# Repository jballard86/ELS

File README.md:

# Electronic Lead Screw
    By Jeff Ballard

Anticipated features:
  - Metric / Inch threading
  - Metric / Inch feeding
  - Auto threading with 2 steppers
  - Auto turn to a specified diameter
  - Pendent Control with:
    - Manual Z control
    - Manual X control
  - Radius cutting
  - Ball cutting
  - chamfer cutting
  - Digital Dial replacements (pipe dream)

This Lead Screw is 100% untested at this point, the code works on a test stand that has the following:
  - 24v power supply
  - 12v power supply
  - Custom PCB w/ a Teensy 4.0
  - 1 stepper motor w/Driver
  - 1 DC motor w/encoder
  - various display/interface hardware

PCB is 100% operational on test board.  Cad files to come for mounting all components in a housing for mounting near the lathe.

Lathe installation will happen shortly.

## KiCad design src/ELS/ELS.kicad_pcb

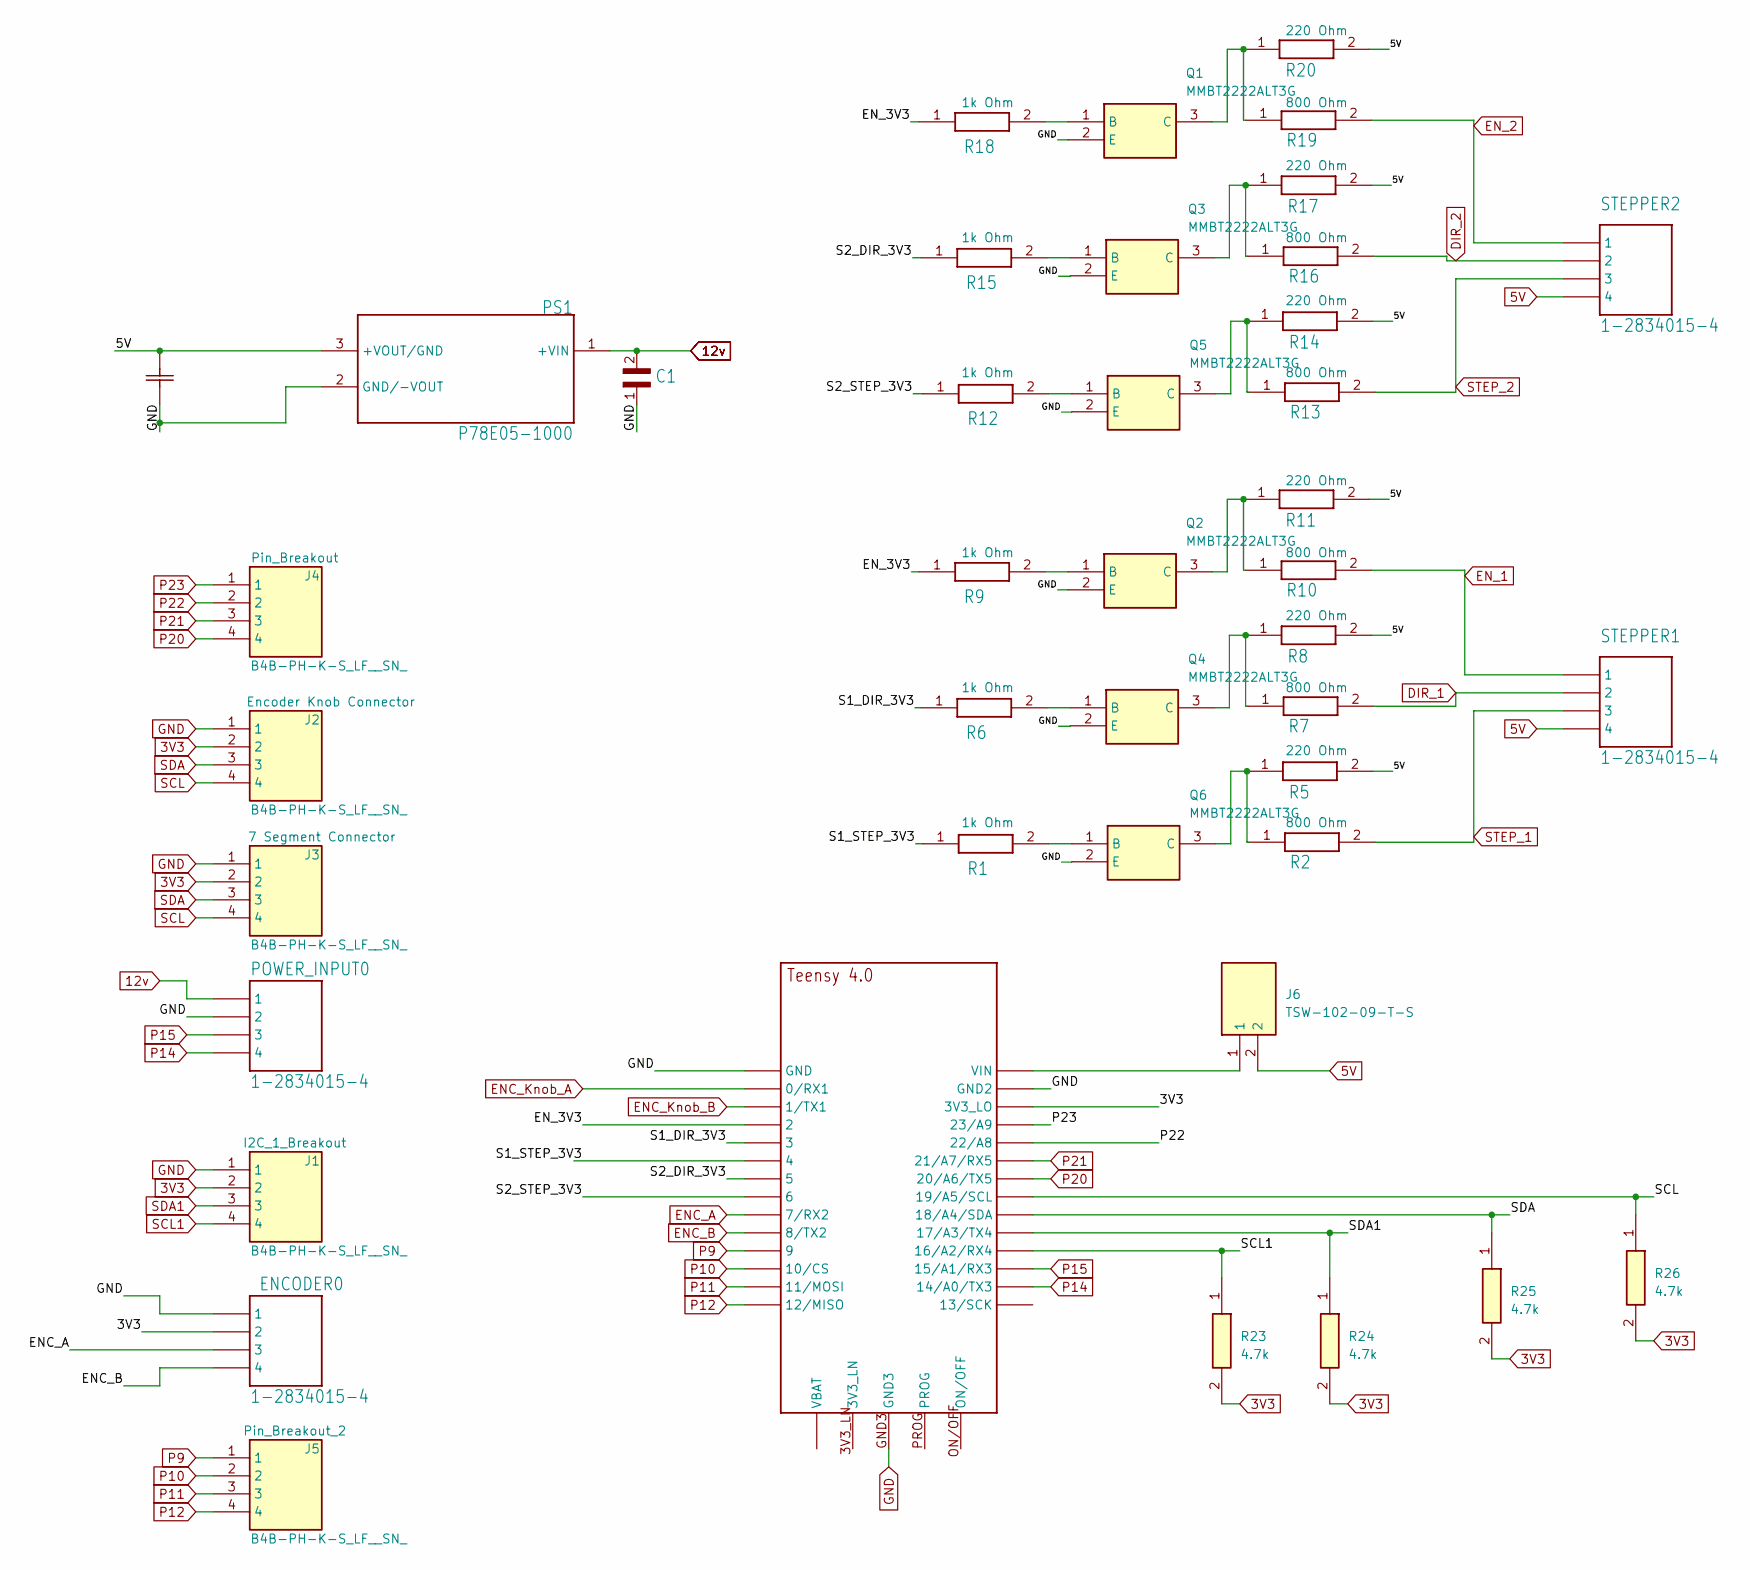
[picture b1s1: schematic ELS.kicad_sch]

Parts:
C1: CL31B106KBHNNNE; CAPC3216X140N
C2: CL32B226MOJNNNECAP_CL32_SAM-M; CAP_CL32_SAM-M
ENCODER0: 1-2834015-4; TE_1-2834015-4
J1, J2, J3, J4, J5: B4B-PH-K-S_LF__SN_; SHDR4W50P0X200_1X4_990X450X600P; Manufacturer_Part_Number B4B-PH-K-S(LF)(SN)
J6: TSW-102-09-T-S; TSW-102-XX-YY-S; Manufacturer_Part_Number TSW-102-09-T-S
POWER_INPUT0: 1-2834015-4; TE_1-2834015-4
PS1: P78E05-1000; CONV_P78E05-1000; VOLTAGE 5v
Q1, Q2, Q3, Q4, Q5, Q6: MMBT2222ALT3G; SOT96P237X111-3N; Mouser Part Number 863-MMBT2222ALT3G
R1, R6, R9, R12, R15, R18: CRCW12061K00FKEAC; RESC3216X60N
R2, R7, R10, R13, R16, R19: CR1206-FX-8250ELF; RESC3216X75N
R5, R8, R11, R14, R17, R20: CRCW1206220RFKEAC; RESC3216X60N
R23, R24, R25, R26: CRCW12064K70FKEBC; RESC3216X60N; Mouser Part Number 71-CRCW12064K70FKEBC
STEPPER1, STEPPER2: 1-2834015-4; TE_1-2834015-4
TEENSY_4.0: TEENSY_4.0

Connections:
3V3: ENCODER0.2_1 (2), ENCODER0.2_2 (2), J1.2, J2.2, J3.2, R23.2, R24.2, R25.2, R26.2, TEENSY_4.0.3V3_LO
5V: C2.2, J6.2, PS1.3 (+VOUT/GND), R5.2, R8.2, R11.2, R14.2, R17.2, R20.2, STEPPER1.4_1 (4), STEPPER1.4_2 (4), STEPPER2.4_1 (4), STEPPER2.4_2 (4)
12v: C1.2, POWER_INPUT0.1_1 (1), POWER_INPUT0.1_2 (1), PS1.1 (+VIN)
/EN_3V3: R9.1, R18.1, TEENSY_4.0.2
/S1_DIR_3V3: R6.1, TEENSY_4.0.3/CANTX (3)
/S1_STEP_3V3: R1.1, TEENSY_4.0.4/CANRX (4)
/S2_DIR_3V3: R15.1, TEENSY_4.0.5
/S2_STEP_3V3: R12.1, TEENSY_4.0.6
DIR_1: R7.2, STEPPER1.2_1 (2), STEPPER1.2_2 (2)
DIR_2: R16.2, STEPPER2.2_1 (2), STEPPER2.2_2 (2)
ENC_A: ENCODER0.3_1 (3), ENCODER0.3_2 (3), TEENSY_4.0.7 (7/RX2)
ENC_B: ENCODER0.4_1 (4), ENCODER0.4_2 (4), TEENSY_4.0.8 (8/TX2)
ENC_Knob_A: TEENSY_4.0.0/RX (0/RX1)
ENC_Knob_B: TEENSY_4.0.1/TX (1/TX1)
EN_1: R10.2, STEPPER1.1_1 (1), STEPPER1.1_2 (1)
EN_2: R19.2, STEPPER2.1_1 (1), STEPPER2.1_2 (1)
GND: C1.1, C2.1, ENCODER0.1_1 (1), ENCODER0.1_2 (1), J1.1, J2.1, J3.1, POWER_INPUT0.2_1 (2), POWER_INPUT0.2_2 (2), PS1.2 (GND/-VOUT), Q1.2 (E), Q2.2 (E), Q3.2 (E), Q4.2 (E), Q5.2 (E), Q6.2 (E), TEENSY_4.0.GND, TEENSY_4.0.GND2, TEENSY_4.0.GND3
unnamed: J6.1, TEENSY_4.0.VIN
unnamed: Q1.1 (B), R18.2
unnamed: Q1.3 (C), R19.1, R20.1
unnamed: Q2.1 (B), R9.2
unnamed: Q2.3 (C), R10.1, R11.1
unnamed: Q3.1 (B), R15.2
unnamed: Q3.3 (C), R16.1, R17.1
unnamed: Q4.1 (B), R6.2
unnamed: Q4.3 (C), R7.1, R8.1
unnamed: Q5.1 (B), R12.2
unnamed: Q5.3 (C), R13.1, R14.1
unnamed: Q6.1 (B), R1.2
unnamed: Q6.3 (C), R2.1, R5.1
P9: J5.1, TEENSY_4.0.9/CS (9)
P10: J5.2, TEENSY_4.0.10/CS
P11: J5.3, TEENSY_4.0.11/MOSI
P12: J5.4, TEENSY_4.0.12/MISO
P14: POWER_INPUT0.4_1 (4), POWER_INPUT0.4_2 (4), TEENSY_4.0.14/A0 (14/A0/TX3)
P15: POWER_INPUT0.3_1 (3), POWER_INPUT0.3_2 (3), TEENSY_4.0.15/A1 (15/A1/RX3)
P20: J4.4, TEENSY_4.0.20/A6 (20/A6/TX5)
P21: J4.3, TEENSY_4.0.21/A7 (21/A7/RX5)
P22: J4.2, TEENSY_4.0.22/A8
P23: J4.1, TEENSY_4.0.23/A9
SCL: J2.4, J3.4, R26.1, TEENSY_4.0.19/A5/SCL
SCL1: J1.4, R23.1, TEENSY_4.0.16/A2 (16/A2/RX4)
SDA: J2.3, J3.3, R25.1, TEENSY_4.0.18/A4/SDA
SDA1: J1.3, R24.1, TEENSY_4.0.17/A3 (17/A3/TX4)
STEP_1: R2.2, STEPPER1.3_1 (3), STEPPER1.3_2 (3)
STEP_2: R13.2, STEPPER2.3_1 (3), STEPPER2.3_2 (3)

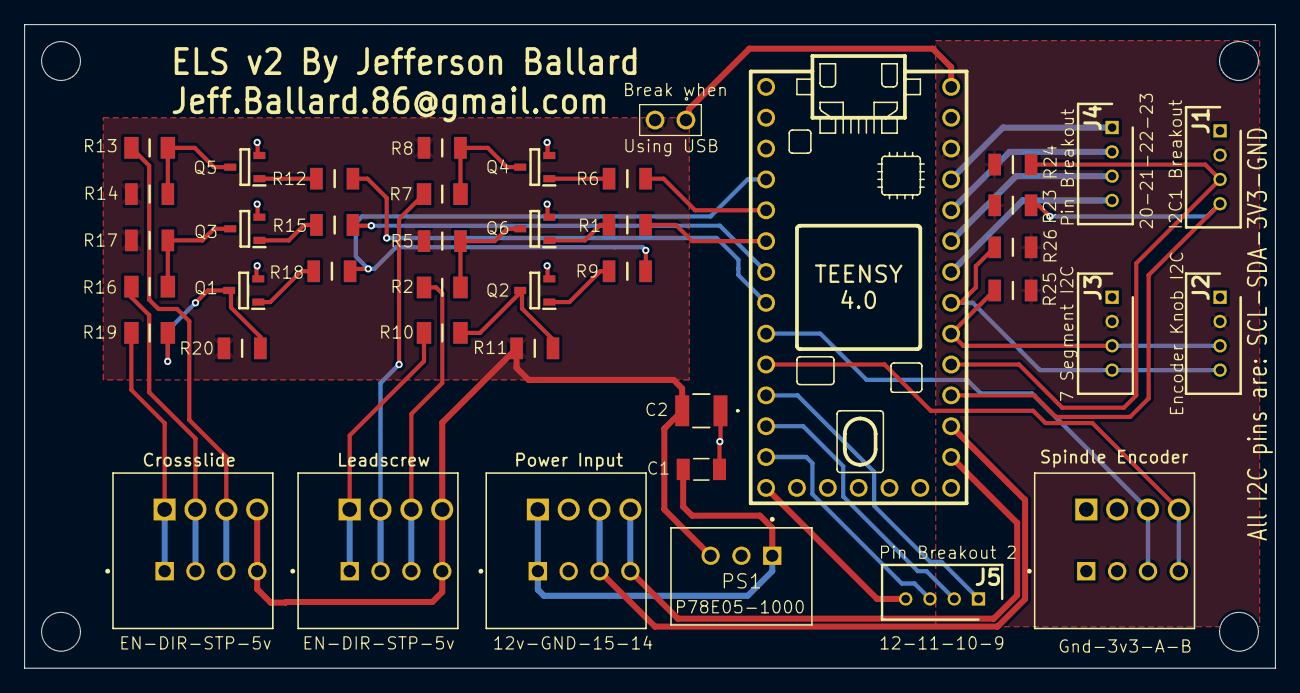
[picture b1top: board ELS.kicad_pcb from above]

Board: 2 copper layers, 103.0 x 53.0 mm, 42 parts (0 on the bottom side), 44 nets.

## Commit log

2023-05-29 initial
2023-05-29 test
2023-05-29 added auto thread menu, and thread depth calcs
2023-05-29 fixed thread depth calculations
2023-05-29 tidying up
2023-05-29 started sub menus
2023-05-30 Auto Threading Submenu additions/tuning
2023-05-30 submenu changes
2023-05-30 finished auto thread sub menu
2023-05-30 "finished" spindle angle code/math
2023-05-30 Create LICENSE
2023-05-30 Update LICENSE
2023-05-30 changed directory structure
2023-05-31 Auto Turn Menu/Interface complete
2023-05-31 fillet
2023-05-31 tidy up
2023-06-01 Fixed Menu Bugs + Tweaks
2023-06-01 Radius Main Menu Complete
2023-06-01 Radius Sub Menu options added
2023-06-01 variables
2023-06-01 fixed unknown error
2023-06-02 started X chord array fill
2023-06-02 Radius Array Building loops added
2023-06-02 counter
2023-06-03 Radius Mode interface started
2023-06-03 Added current 3d cad data
2023-06-03 changed folder name
2023-06-03 restructure
2023-06-03 revert
2023-06-03 Replacced Continuous Stepper with Accelstepper
2023-06-03 count
2023-06-03 adjusted variables
2023-06-03 pre merge
2023-06-04 Accelstepper and new PCB Update
2023-06-04 Cad Update
    Enclosure nearly complete
2023-06-04 Tweaks, no major changes
2023-06-04 auto radius graphic update
2023-06-05 ELS Housing Files Complete
2023-06-05 Enclosure tweaks
2023-06-05 fixed step rate, tweaked auto radius graphics
2023-06-06 auto radius menu additions
2023-06-06 removed parametric files
    only uploading STL files for enclosure, will likely add step files at a later date
2023-06-06 Added MultiStepper Support and variables
2023-06-07 nothing in particular
2023-06-07 Lathe Coordinate correction
    changed coordinates from XY to ZY
2023-06-07 Fixed Cut_Pass
    The math in the Cut_Pass function was incorrect.
    Added support for all radius types.
2023-06-07 Build_XY_Array
    Finished the ZY array so that all points for all radius types are
    accurate for the finished radius.
2023-06-08 Auto_Radius()
    Rough cut is ready to try on lathe.
    Final pass is not ready.
    Submenu for auto_radius() is not complete and has errors still.
2023-06-08 Tweaks - simplified the code in Feed.h and Thread.h added accelstepper run comands to each mode depending on needs added comments to functions
2023-06-11 Auto Radius movement code update
2023-06-11 Auto Radius Tweaks
2023-06-11 Finished Auto_Radius submenu
